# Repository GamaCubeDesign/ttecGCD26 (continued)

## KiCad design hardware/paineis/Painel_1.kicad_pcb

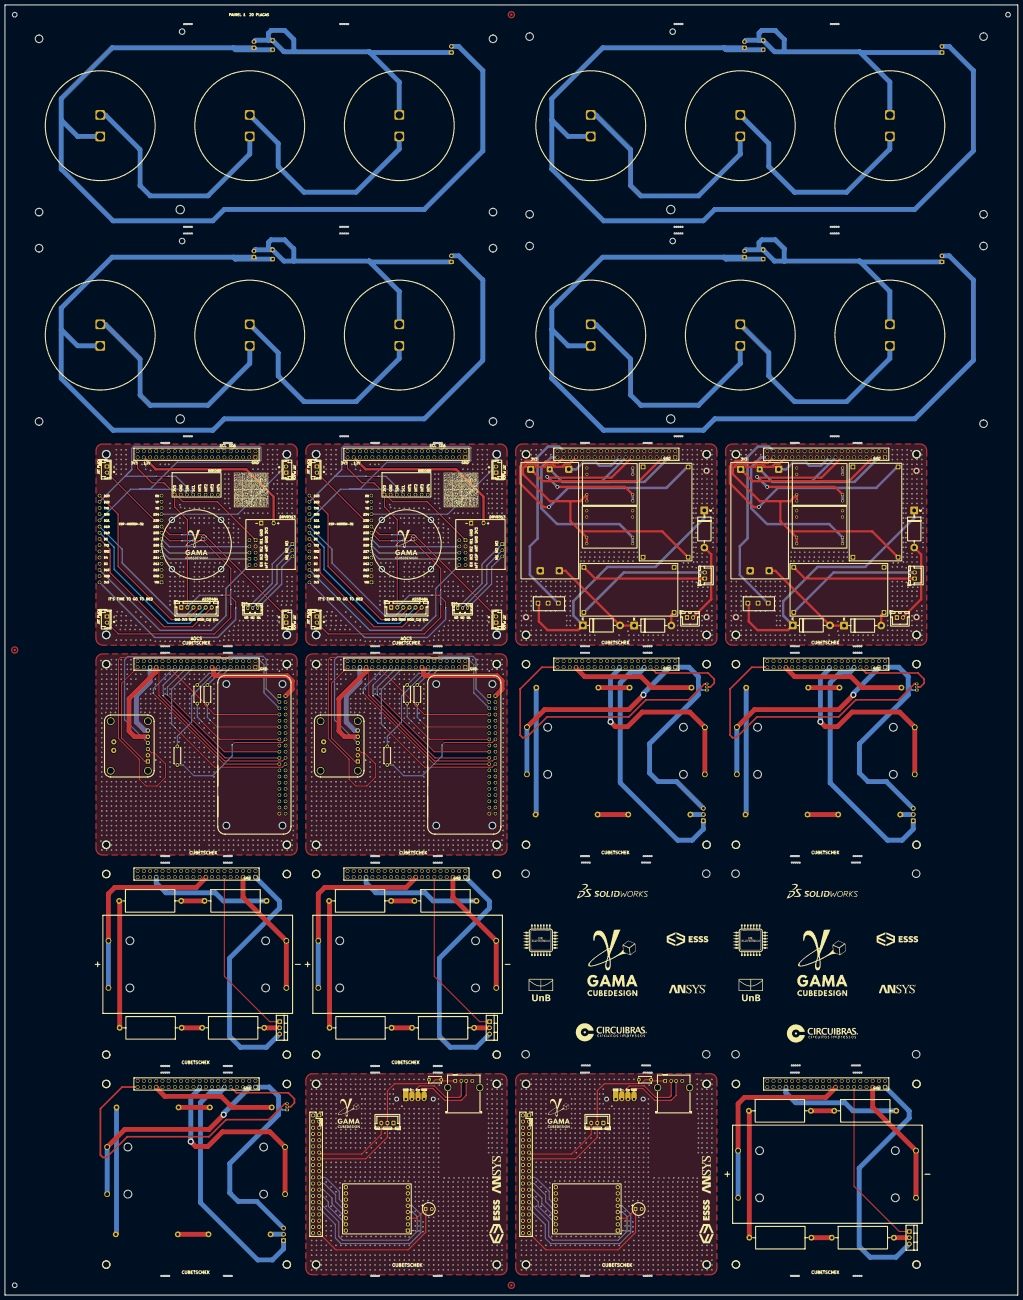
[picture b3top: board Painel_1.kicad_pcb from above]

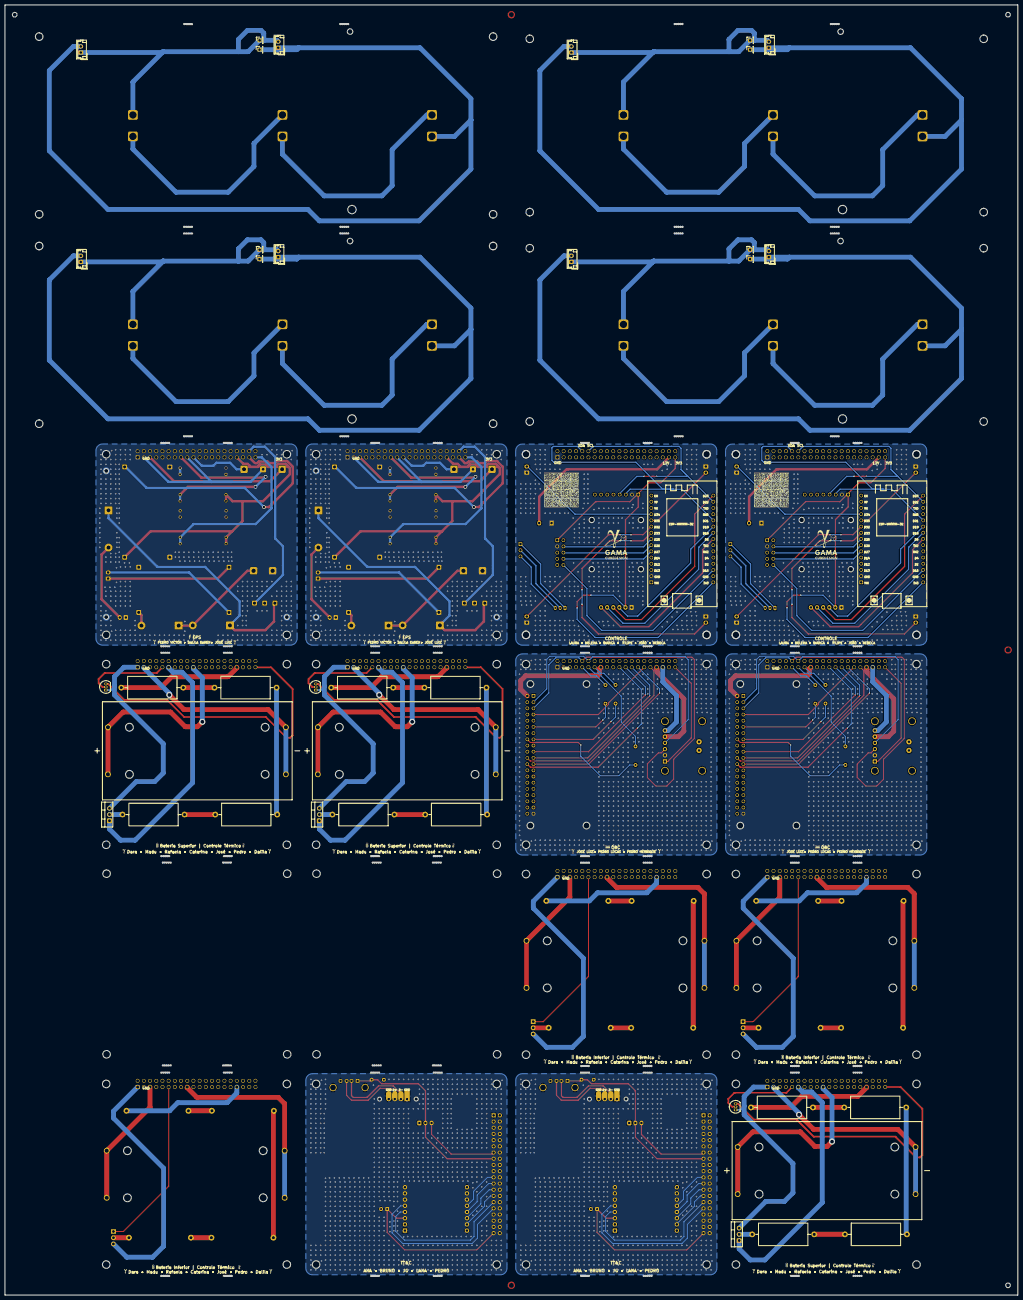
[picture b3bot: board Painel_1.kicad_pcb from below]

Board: 2 copper layers, 415.0 x 528.6 mm, 669 parts (79 on the bottom side), 208 nets.

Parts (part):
AOCS_1_1_AS5048A2, AOCS_2_1_AS5048A2: AS5048A
AOCS_1_2_REF**, AOCS_1_4_REF**, AOCS_1_7_REF**, AOCS_1_9_REF**, AOCS_2_2_REF**, AOCS_2_4_REF**, AOCS_2_7_REF**, AOCS_2_9_REF**: furo
AOCS_1_3_DRV8313, AOCS_2_3_DRV8313: DRV8313; DRV3813
AOCS_1_5_X+1, AOCS_1_12_Y-1, AOCS_1_13_X-1, AOCS_1_14_Y+1, AOCS_2_5_X+1, AOCS_2_12_Y-1, AOCS_2_13_X-1, AOCS_2_14_Y+1: JST; JST_PLACA
AOCS_1_6_Barramento1, AOCS_2_6_Barramento1: Barramento
AOCS_1_8_logo, AOCS_1_18_logo, AOCS_2_8_logo, AOCS_2_18_logo: LOGO; logo
AOCS_1_10_G***, AOCS_1_17_G***, AOCS_2_10_G***, AOCS_2_17_G***: LOGO; data
AOCS_1_11_GM2804, AOCS_2_11_GM2804: GM2804; GM2804_Molex_KK-3p-254
AOCS_1_15_BMI008, AOCS_2_15_BMI008: BMI088
AOCS_1_16_ESP32, AOCS_2_16_ESP32: ESP32; ESP32-30p
EPS_1_1_D3, EPS_1_12_D2, EPS_1_16_D1, EPS_2_1_D3, EPS_2_12_D2, EPS_2_16_D1: 1N5822; D_DO-201AD_P15.24mm_Horizontal
EPS_1_2_MP1584_Module2, EPS_1_4_MP1584_Module1, EPS_2_2_MP1584_Module2, EPS_2_4_MP1584_Module1: MP1584_MODULE
EPS_1_3_J3, EPS_1_17_J2, EPS_2_3_J3, EPS_2_17_J2: Conn_01x02_Pin; JST_XH_B2B-XH-A_1x02_P2.50mm_Vertical
EPS_1_5_G***, EPS_1_18_G***, EPS_1_19_G***, EPS_1_20_G***, EPS_1_CIMA_1_7_G***, EPS_1_CIMA_1_9_G***, EPS_1_CIMA_1_10_G***, EPS_1_CIMA_1_16_G***, EPS_1_CIMA_2_7_G***, EPS_1_CIMA_2_9_G***, EPS_1_CIMA_2_10_G***, EPS_1_CIMA_2_16_G***, EPS_1_CIMA_3_7_G***, EPS_1_CIMA_3_9_G***, EPS_1_CIMA_3_10_G***, EPS_1_CIMA_3_16_G***, EPS_2_5_G***, EPS_2_18_G***, EPS_2_19_G***, EPS_2_20_G***, EPS_2_BAIXO_1_12_G***, EPS_2_BAIXO_1_13_G***, EPS_2_BAIXO_1_14_G***, EPS_2_BAIXO_1_15_G***, EPS_2_BAIXO_2_12_G***, EPS_2_BAIXO_2_13_G***, EPS_2_BAIXO_2_14_G***, EPS_2_BAIXO_2_15_G***, EPS_2_BAIXO_3_12_G***, EPS_2_BAIXO_3_13_G***, EPS_2_BAIXO_3_14_G***, EPS_2_BAIXO_3_15_G***: LOGO
EPS_1_6_, EPS_1_9_, EPS_1_11_, EPS_1_13_, EPS_1_CIMA_1_1_, EPS_1_CIMA_1_3_, EPS_1_CIMA_1_4_, EPS_1_CIMA_1_5_, EPS_1_CIMA_2_1_, EPS_1_CIMA_2_3_, EPS_1_CIMA_2_4_, EPS_1_CIMA_2_5_, EPS_1_CIMA_3_1_, EPS_1_CIMA_3_3_, EPS_1_CIMA_3_4_, EPS_1_CIMA_3_5_, EPS_2_6_, EPS_2_9_, EPS_2_11_, EPS_2_13_, EPS_2_BAIXO_1_3_, EPS_2_BAIXO_1_6_, EPS_2_BAIXO_1_8_, EPS_2_BAIXO_1_11_, EPS_2_BAIXO_2_3_, EPS_2_BAIXO_2_6_, EPS_2_BAIXO_2_8_, EPS_2_BAIXO_2_11_, EPS_2_BAIXO_3_3_, EPS_2_BAIXO_3_6_, EPS_2_BAIXO_3_8_, EPS_2_BAIXO_3_11_: MountingHole_3.20mm
EPS_1_7_J1, EPS_1_CIMA_1_2_J1, EPS_1_CIMA_2_2_J1, EPS_1_CIMA_3_2_J1, EPS_2_7_J1, EPS_2_BAIXO_1_4_J1, EPS_2_BAIXO_2_4_J1, EPS_2_BAIXO_3_4_J1: Conn_02x20_Odd_Even; PC104_PSTD-2.54-2X20P
EPS_1_8_BMS-HX-2S-JH20, EPS_2_8_BMS-HX-2S-JH20: HX-2S-JH20
EPS_1_10_U1, EPS_1_15_U2, EPS_2_10_U1, EPS_2_15_U2: TPS61088
EPS_1_14_SW1, EPS_2_14_SW1: SW_SPDT; KW10
EPS_1_CIMA_1_6_Q1, EPS_1_CIMA_2_6_Q1, EPS_1_CIMA_3_6_Q1, EPS_2_BAIXO_1_5_Q1, EPS_2_BAIXO_2_5_Q1, EPS_2_BAIXO_3_5_Q1: TIP120; TO-220-3_Vertical
EPS_1_CIMA_1_8_R1, EPS_1_CIMA_1_11_R3, EPS_1_CIMA_1_12_R2, EPS_1_CIMA_1_15_R4, EPS_1_CIMA_2_8_R1, EPS_1_CIMA_2_11_R3, EPS_1_CIMA_2_12_R2, EPS_1_CIMA_2_15_R4, EPS_1_CIMA_3_8_R1, EPS_1_CIMA_3_11_R3, EPS_1_CIMA_3_12_R2, EPS_1_CIMA_3_15_R4, EPS_2_BAIXO_1_1_R2, EPS_2_BAIXO_1_2_R1, EPS_2_BAIXO_1_9_R3, EPS_2_BAIXO_1_10_R4, EPS_2_BAIXO_2_1_R2, EPS_2_BAIXO_2_2_R1, EPS_2_BAIXO_2_9_R3, EPS_2_BAIXO_2_10_R4, EPS_2_BAIXO_3_1_R2, EPS_2_BAIXO_3_2_R1, EPS_2_BAIXO_3_9_R3, EPS_2_BAIXO_3_10_R4: Heater; R_Axial_DIN0922_L20.0mm_D9.0mm_P25.40mm_Horizontal
EPS_1_CIMA_1_13_BT1, EPS_1_CIMA_2_13_BT1, EPS_1_CIMA_3_13_BT1, EPS_2_BAIXO_1_7_BT1, EPS_2_BAIXO_2_7_BT1, EPS_2_BAIXO_3_7_BT1: BK-18650-PC4; BAT_BK-18650-PC4
EPS_1_CIMA_1_14_U1, EPS_1_CIMA_2_14_U1, EPS_1_CIMA_3_14_U1: DS18B20; TO-92_Inline
FID_1_1, FID_1_2, FID_1_3: Fiducial_Donut_1_2_3
MB_AOCS_1_bottom_1_1, MB_AOCS_1_bottom_1_2, MB_AOCS_1_bottom_1_3, MB_AOCS_1_bottom_1_4, MB_AOCS_1_bottom_1_5, MB_AOCS_1_bottom_2_1, MB_AOCS_1_bottom_2_2, MB_AOCS_1_bottom_2_3, MB_AOCS_1_bottom_2_4, MB_AOCS_1_bottom_2_5, MB_AOCS_1_top_1_1, MB_AOCS_1_top_1_2, MB_AOCS_1_top_1_3, MB_AOCS_1_top_1_4, MB_AOCS_1_top_1_5, MB_AOCS_1_top_2_1, MB_AOCS_1_top_2_2, MB_AOCS_1_top_2_3, MB_AOCS_1_top_2_4, MB_AOCS_1_top_2_5, MB_AOCS_2_bottom_1_1, MB_AOCS_2_bottom_1_2, MB_AOCS_2_bottom_1_3, MB_AOCS_2_bottom_1_4, MB_AOCS_2_bottom_1_5, MB_AOCS_2_bottom_2_1, MB_AOCS_2_bottom_2_2, MB_AOCS_2_bottom_2_3, MB_AOCS_2_bottom_2_4, MB_AOCS_2_bottom_2_5, MB_AOCS_2_top_1_1, MB_AOCS_2_top_1_2, MB_AOCS_2_top_1_3, MB_AOCS_2_top_1_4, MB_AOCS_2_top_1_5, MB_AOCS_2_top_2_1, MB_AOCS_2_top_2_2, MB_AOCS_2_top_2_3, MB_AOCS_2_top_2_4, MB_AOCS_2_top_2_5: NPTH
MB_EPS_1_CIMA_1_bottom_1_1, MB_EPS_1_CIMA_1_bottom_1_2, MB_EPS_1_CIMA_1_bottom_1_3, MB_EPS_1_CIMA_1_bottom_1_4, MB_EPS_1_CIMA_1_bottom_1_5, MB_EPS_1_CIMA_1_bottom_2_1, MB_EPS_1_CIMA_1_bottom_2_2, MB_EPS_1_CIMA_1_bottom_2_3, MB_EPS_1_CIMA_1_bottom_2_4, MB_EPS_1_CIMA_1_bottom_2_5, MB_EPS_1_CIMA_1_top_1_1, MB_EPS_1_CIMA_1_top_1_2, MB_EPS_1_CIMA_1_top_1_3, MB_EPS_1_CIMA_1_top_1_4, MB_EPS_1_CIMA_1_top_1_5, MB_EPS_1_CIMA_1_top_2_1, MB_EPS_1_CIMA_1_top_2_2, MB_EPS_1_CIMA_1_top_2_3, MB_EPS_1_CIMA_1_top_2_4, MB_EPS_1_CIMA_1_top_2_5, MB_EPS_1_CIMA_2_bottom_1_1, MB_EPS_1_CIMA_2_bottom_1_2, MB_EPS_1_CIMA_2_bottom_1_3, MB_EPS_1_CIMA_2_bottom_1_4, MB_EPS_1_CIMA_2_bottom_1_5, MB_EPS_1_CIMA_2_bottom_2_1, MB_EPS_1_CIMA_2_bottom_2_2, MB_EPS_1_CIMA_2_bottom_2_3, MB_EPS_1_CIMA_2_bottom_2_4, MB_EPS_1_CIMA_2_bottom_2_5, MB_EPS_1_CIMA_2_top_1_1, MB_EPS_1_CIMA_2_top_1_2, MB_EPS_1_CIMA_2_top_1_3, MB_EPS_1_CIMA_2_top_1_4, MB_EPS_1_CIMA_2_top_1_5, MB_EPS_1_CIMA_2_top_2_1, MB_EPS_1_CIMA_2_top_2_2, MB_EPS_1_CIMA_2_top_2_3, MB_EPS_1_CIMA_2_top_2_4, MB_EPS_1_CIMA_2_top_2_5, MB_EPS_1_CIMA_3_bottom_1_1, MB_EPS_1_CIMA_3_bottom_1_2, MB_EPS_1_CIMA_3_bottom_1_3, MB_EPS_1_CIMA_3_bottom_1_4, MB_EPS_1_CIMA_3_bottom_1_5, MB_EPS_1_CIMA_3_bottom_2_1, MB_EPS_1_CIMA_3_bottom_2_2, MB_EPS_1_CIMA_3_bottom_2_3, MB_EPS_1_CIMA_3_bottom_2_4, MB_EPS_1_CIMA_3_bottom_2_5, MB_EPS_1_CIMA_3_top_1_1, MB_EPS_1_CIMA_3_top_1_2, MB_EPS_1_CIMA_3_top_1_3, MB_EPS_1_CIMA_3_top_1_4, MB_EPS_1_CIMA_3_top_1_5, MB_EPS_1_CIMA_3_top_2_1, MB_EPS_1_CIMA_3_top_2_2, MB_EPS_1_CIMA_3_top_2_3, MB_EPS_1_CIMA_3_top_2_4, MB_EPS_1_CIMA_3_top_2_5, MB_EPS_1_bottom_1_1, MB_EPS_1_bottom_1_2, MB_EPS_1_bottom_1_3, MB_EPS_1_bottom_1_4, MB_EPS_1_bottom_1_5, MB_EPS_1_bottom_2_1, MB_EPS_1_bottom_2_2, MB_EPS_1_bottom_2_3, MB_EPS_1_bottom_2_4, MB_EPS_1_bottom_2_5, MB_EPS_1_top_1_1, MB_EPS_1_top_1_2, MB_EPS_1_top_1_3, MB_EPS_1_top_1_4, MB_EPS_1_top_1_5, MB_EPS_1_top_2_1, MB_EPS_1_top_2_2, MB_EPS_1_top_2_3, MB_EPS_1_top_2_4, MB_EPS_1_top_2_5, MB_EPS_2_BAIXO_1_bottom_1_1, MB_EPS_2_BAIXO_1_bottom_1_2, MB_EPS_2_BAIXO_1_bottom_1_3, MB_EPS_2_BAIXO_1_bottom_1_4, MB_EPS_2_BAIXO_1_bottom_1_5, MB_EPS_2_BAIXO_1_bottom_2_1, MB_EPS_2_BAIXO_1_bottom_2_2, MB_EPS_2_BAIXO_1_bottom_2_3, MB_EPS_2_BAIXO_1_bottom_2_4, MB_EPS_2_BAIXO_1_bottom_2_5, MB_EPS_2_BAIXO_1_top_1_1, MB_EPS_2_BAIXO_1_top_1_2, MB_EPS_2_BAIXO_1_top_1_3, MB_EPS_2_BAIXO_1_top_1_4, MB_EPS_2_BAIXO_1_top_1_5, MB_EPS_2_BAIXO_1_top_2_1, MB_EPS_2_BAIXO_1_top_2_2, MB_EPS_2_BAIXO_1_top_2_3, MB_EPS_2_BAIXO_1_top_2_4, MB_EPS_2_BAIXO_1_top_2_5, MB_EPS_2_BAIXO_2_bottom_1_1, MB_EPS_2_BAIXO_2_bottom_1_2, MB_EPS_2_BAIXO_2_bottom_1_3, MB_EPS_2_BAIXO_2_bottom_1_4, MB_EPS_2_BAIXO_2_bottom_1_5, MB_EPS_2_BAIXO_2_bottom_2_1, MB_EPS_2_BAIXO_2_bottom_2_2, MB_EPS_2_BAIXO_2_bottom_2_3, MB_EPS_2_BAIXO_2_bottom_2_4, MB_EPS_2_BAIXO_2_bottom_2_5, MB_EPS_2_BAIXO_2_top_1_1, MB_EPS_2_BAIXO_2_top_1_2, MB_EPS_2_BAIXO_2_top_1_3, MB_EPS_2_BAIXO_2_top_1_4, MB_EPS_2_BAIXO_2_top_1_5, MB_EPS_2_BAIXO_2_top_2_1, MB_EPS_2_BAIXO_2_top_2_2, MB_EPS_2_BAIXO_2_top_2_3, MB_EPS_2_BAIXO_2_top_2_4, MB_EPS_2_BAIXO_2_top_2_5, MB_EPS_2_BAIXO_3_bottom_1_1, MB_EPS_2_BAIXO_3_bottom_1_2, MB_EPS_2_BAIXO_3_bottom_1_3, MB_EPS_2_BAIXO_3_bottom_1_4, MB_EPS_2_BAIXO_3_bottom_1_5, MB_EPS_2_BAIXO_3_bottom_2_1, MB_EPS_2_BAIXO_3_bottom_2_2, MB_EPS_2_BAIXO_3_bottom_2_3, MB_EPS_2_BAIXO_3_bottom_2_4, MB_EPS_2_BAIXO_3_bottom_2_5, MB_EPS_2_BAIXO_3_top_1_1, MB_EPS_2_BAIXO_3_top_1_2, MB_EPS_2_BAIXO_3_top_1_3, MB_EPS_2_BAIXO_3_top_1_4, MB_EPS_2_BAIXO_3_top_1_5, MB_EPS_2_BAIXO_3_top_2_1, MB_EPS_2_BAIXO_3_top_2_2, MB_EPS_2_BAIXO_3_top_2_3, MB_EPS_2_BAIXO_3_top_2_4, MB_EPS_2_BAIXO_3_top_2_5, MB_EPS_2_bottom_1_1, MB_EPS_2_bottom_1_2, MB_EPS_2_bottom_1_3, MB_EPS_2_bottom_1_4, MB_EPS_2_bottom_1_5, MB_EPS_2_bottom_2_1, MB_EPS_2_bottom_2_2, MB_EPS_2_bottom_2_3, MB_EPS_2_bottom_2_4, MB_EPS_2_bottom_2_5, MB_EPS_2_top_1_1, MB_EPS_2_top_1_2, MB_EPS_2_top_1_3, MB_EPS_2_top_1_4, MB_EPS_2_top_1_5, MB_EPS_2_top_2_1, MB_EPS_2_top_2_2, MB_EPS_2_top_2_3, MB_EPS_2_top_2_4, MB_EPS_2_top_2_5: NPTH
MB_OBC_1_bottom_1_1, MB_OBC_1_bottom_1_2, MB_OBC_1_bottom_1_3, MB_OBC_1_bottom_1_4, MB_OBC_1_bottom_1_5, MB_OBC_1_bottom_2_1, MB_OBC_1_bottom_2_2, MB_OBC_1_bottom_2_3, MB_OBC_1_bottom_2_4, MB_OBC_1_bottom_2_5, MB_OBC_1_top_1_1, MB_OBC_1_top_1_2, MB_OBC_1_top_1_3, MB_OBC_1_top_1_4, MB_OBC_1_top_1_5, MB_OBC_1_top_2_1, MB_OBC_1_top_2_2, MB_OBC_1_top_2_3, MB_OBC_1_top_2_4, MB_OBC_1_top_2_5, MB_OBC_2_bottom_1_1, MB_OBC_2_bottom_1_2, MB_OBC_2_bottom_1_3, MB_OBC_2_bottom_1_4, MB_OBC_2_bottom_1_5, MB_OBC_2_bottom_2_1, MB_OBC_2_bottom_2_2, MB_OBC_2_bottom_2_3, MB_OBC_2_bottom_2_4, MB_OBC_2_bottom_2_5, MB_OBC_2_top_1_1, MB_OBC_2_top_1_2, MB_OBC_2_top_1_3, MB_OBC_2_top_1_4, MB_OBC_2_top_1_5, MB_OBC_2_top_2_1, MB_OBC_2_top_2_2, MB_OBC_2_top_2_3, MB_OBC_2_top_2_4, MB_OBC_2_top_2_5: NPTH
MB_SOLAR_1_1_bottom_1_1, MB_SOLAR_1_1_bottom_1_2, MB_SOLAR_1_1_bottom_1_3, MB_SOLAR_1_1_bottom_1_4, MB_SOLAR_1_1_bottom_1_5, MB_SOLAR_1_1_bottom_2_1, MB_SOLAR_1_1_bottom_2_2, MB_SOLAR_1_1_bottom_2_3, MB_SOLAR_1_1_bottom_2_4, MB_SOLAR_1_1_bottom_2_5, MB_SOLAR_1_1_top_1_1, MB_SOLAR_1_1_top_1_2, MB_SOLAR_1_1_top_1_3, MB_SOLAR_1_1_top_1_4, MB_SOLAR_1_1_top_1_5, MB_SOLAR_1_1_top_2_1, MB_SOLAR_1_1_top_2_2, MB_SOLAR_1_1_top_2_3, MB_SOLAR_1_1_top_2_4, MB_SOLAR_1_1_top_2_5, MB_SOLAR_1_2_bottom_1_1, MB_SOLAR_1_2_bottom_1_2, MB_SOLAR_1_2_bottom_1_3, MB_SOLAR_1_2_bottom_1_4, MB_SOLAR_1_2_bottom_1_5, MB_SOLAR_1_2_bottom_2_1, MB_SOLAR_1_2_bottom_2_2, MB_SOLAR_1_2_bottom_2_3, MB_SOLAR_1_2_bottom_2_4, MB_SOLAR_1_2_bottom_2_5, MB_SOLAR_1_2_top_1_1, MB_SOLAR_1_2_top_1_2, MB_SOLAR_1_2_top_1_3, MB_SOLAR_1_2_top_1_4, MB_SOLAR_1_2_top_1_5, MB_SOLAR_1_2_top_2_1, MB_SOLAR_1_2_top_2_2, MB_SOLAR_1_2_top_2_3, MB_SOLAR_1_2_top_2_4, MB_SOLAR_1_2_top_2_5, MB_SOLAR_2_1_bottom_1_1, MB_SOLAR_2_1_bottom_1_2, MB_SOLAR_2_1_bottom_1_3, MB_SOLAR_2_1_bottom_1_4, MB_SOLAR_2_1_bottom_1_5, MB_SOLAR_2_1_bottom_2_1, MB_SOLAR_2_1_bottom_2_2, MB_SOLAR_2_1_bottom_2_3, MB_SOLAR_2_1_bottom_2_4, MB_SOLAR_2_1_bottom_2_5, MB_SOLAR_2_1_top_1_1, MB_SOLAR_2_1_top_1_2, MB_SOLAR_2_1_top_1_3, MB_SOLAR_2_1_top_1_4, MB_SOLAR_2_1_top_1_5, MB_SOLAR_2_1_top_2_1, MB_SOLAR_2_1_top_2_2, MB_SOLAR_2_1_top_2_3, MB_SOLAR_2_1_top_2_4, MB_SOLAR_2_1_top_2_5, MB_SOLAR_2_2_bottom_1_1, MB_SOLAR_2_2_bottom_1_2, MB_SOLAR_2_2_bottom_1_3, MB_SOLAR_2_2_bottom_1_4, MB_SOLAR_2_2_bottom_1_5, MB_SOLAR_2_2_bottom_2_1, MB_SOLAR_2_2_bottom_2_2, MB_SOLAR_2_2_bottom_2_3, MB_SOLAR_2_2_bottom_2_4, MB_SOLAR_2_2_bottom_2_5, MB_SOLAR_2_2_top_1_1, MB_SOLAR_2_2_top_1_2, MB_SOLAR_2_2_top_1_3, MB_SOLAR_2_2_top_1_4, MB_SOLAR_2_2_top_1_5, MB_SOLAR_2_2_top_2_1, MB_SOLAR_2_2_top_2_2, MB_SOLAR_2_2_top_2_3, MB_SOLAR_2_2_top_2_4, MB_SOLAR_2_2_top_2_5: NPTH
MB_TTEC_1_bottom_1_1, MB_TTEC_1_bottom_1_2, MB_TTEC_1_bottom_1_3, MB_TTEC_1_bottom_1_4, MB_TTEC_1_bottom_1_5, MB_TTEC_1_bottom_2_1, MB_TTEC_1_bottom_2_2, MB_TTEC_1_bottom_2_3, MB_TTEC_1_bottom_2_4, MB_TTEC_1_bottom_2_5, MB_TTEC_1_top_1_1, MB_TTEC_1_top_1_2, MB_TTEC_1_top_1_3, MB_TTEC_1_top_1_4, MB_TTEC_1_top_1_5, MB_TTEC_1_top_2_1, MB_TTEC_1_top_2_2, MB_TTEC_1_top_2_3, MB_TTEC_1_top_2_4, MB_TTEC_1_top_2_5, MB_TTEC_2_bottom_1_1, MB_TTEC_2_bottom_1_2, MB_TTEC_2_bottom_1_3, MB_TTEC_2_bottom_1_4, MB_TTEC_2_bottom_1_5, MB_TTEC_2_bottom_2_1, MB_TTEC_2_bottom_2_2, MB_TTEC_2_bottom_2_3, MB_TTEC_2_bottom_2_4, MB_TTEC_2_bottom_2_5, MB_TTEC_2_top_1_1, MB_TTEC_2_top_1_2, MB_TTEC_2_top_1_3, MB_TTEC_2_top_1_4, MB_TTEC_2_top_1_5, MB_TTEC_2_top_2_1, MB_TTEC_2_top_2_2, MB_TTEC_2_top_2_3, MB_TTEC_2_top_2_4, MB_TTEC_2_top_2_5: NPTH
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
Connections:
AOCS_1/GND: AOCS_1_1_AS5048A2.1 (GND), AOCS_1_3_DRV8313.1 (GND), AOCS_1_3_DRV8313.14 (GND), AOCS_1_5_X+1.1, AOCS_1_6_Barramento1.1, AOCS_1_12_Y-1.1, AOCS_1_13_X-1.1, AOCS_1_14_Y+1.1, AOCS_1_15_BMI008.2 (GND), AOCS_1_16_ESP32.2 (GND)
AOCS_1/Net-(AS5048A2-3V3): AOCS_1_1_AS5048A2.2 (3V3), AOCS_1_3_DRV8313.15 (3V3), AOCS_1_6_Barramento1.39, AOCS_1_15_BMI008.1 (3.3V), AOCS_1_16_ESP32.16 (3V3)
AOCS_1/Net-(AS5048A2-CLK): AOCS_1_1_AS5048A2.5 (CLK), AOCS_1_16_ESP32.24 (D18)
AOCS_1/Net-(AS5048A2-MISO): AOCS_1_1_AS5048A2.3 (MISO), AOCS_1_16_ESP32.25 (D19)
AOCS_1/Net-(AS5048A2-MOSI): AOCS_1_1_AS5048A2.4 (MOSI), AOCS_1_16_ESP32.30 (D23)
AOCS_1/Net-(AS5048A2-SCn): AOCS_1_1_AS5048A2.6 (SCn), AOCS_1_16_ESP32.23 (D5)
AOCS_1/Net-(BMI008-SCL): AOCS_1_6_Barramento1.12, AOCS_1_15_BMI008.4 (SCL), AOCS_1_16_ESP32.29 (D22)
AOCS_1/Net-(BMI008-SDA): AOCS_1_6_Barramento1.10, AOCS_1_15_BMI008.3 (SDA), AOCS_1_16_ESP32.26 (D21)
AOCS_1/Net-(Barramento1-Pin_37): AOCS_1_3_DRV8313.2 (VIN), AOCS_1_6_Barramento1.37
AOCS_1/Net-(DRV8313-EN): AOCS_1_3_DRV8313.6 (EN), AOCS_1_16_ESP32.18 (D15)
AOCS_1/Net-(DRV8313-IN1): AOCS_1_3_DRV8313.9 (IN1), AOCS_1_16_ESP32.8 (D25)
AOCS_1/Net-(DRV8313-IN2): AOCS_1_3_DRV8313.8 (IN2), AOCS_1_16_ESP32.7 (D26)
AOCS_1/Net-(DRV8313-IN3): AOCS_1_3_DRV8313.7 (IN3), AOCS_1_16_ESP32.6 (D27)
AOCS_1/Net-(DRV8313-M1): AOCS_1_3_DRV8313.3 (M1), AOCS_1_11_GM2804.1 (VIN)
AOCS_1/Net-(DRV8313-M2): AOCS_1_3_DRV8313.4 (M2), AOCS_1_11_GM2804.2 (GND)
AOCS_1/Net-(DRV8313-M3): AOCS_1_3_DRV8313.5 (M3), AOCS_1_11_GM2804.3 (PWM)
AOCS_1/Net-(ESP32-D32): AOCS_1_14_Y+1.2, AOCS_1_16_ESP32.10 (D32)
AOCS_1/Net-(ESP32-D33): AOCS_1_12_Y-1.2, AOCS_1_16_ESP32.9 (D33)
AOCS_1/Net-(ESP32-D34): AOCS_1_5_X+1.2, AOCS_1_16_ESP32.12 (D34)
AOCS_1/Net-(ESP32-D35): AOCS_1_13_X-1.2, AOCS_1_16_ESP32.11 (D35)
AOCS_2/GND: AOCS_2_1_AS5048A2.1 (GND), AOCS_2_3_DRV8313.1 (GND), AOCS_2_3_DRV8313.14 (GND), AOCS_2_5_X+1.1, AOCS_2_6_Barramento1.1, AOCS_2_12_Y-1.1, AOCS_2_13_X-1.1, AOCS_2_14_Y+1.1, AOCS_2_15_BMI008.2 (GND), AOCS_2_16_ESP32.2 (GND)
AOCS_2/Net-(AS5048A2-3V3): AOCS_2_1_AS5048A2.2 (3V3), AOCS_2_3_DRV8313.15 (3V3), AOCS_2_6_Barramento1.39, AOCS_2_15_BMI008.1 (3.3V), AOCS_2_16_ESP32.16 (3V3)
AOCS_2/Net-(AS5048A2-CLK): AOCS_2_1_AS5048A2.5 (CLK), AOCS_2_16_ESP32.24 (D18)
AOCS_2/Net-(AS5048A2-MISO): AOCS_2_1_AS5048A2.3 (MISO), AOCS_2_16_ESP32.25 (D19)
AOCS_2/Net-(AS5048A2-MOSI): AOCS_2_1_AS5048A2.4 (MOSI), AOCS_2_16_ESP32.30 (D23)
AOCS_2/Net-(AS5048A2-SCn): AOCS_2_1_AS5048A2.6 (SCn), AOCS_2_16_ESP32.23 (D5)
AOCS_2/Net-(BMI008-SCL): AOCS_2_6_Barramento1.12, AOCS_2_15_BMI008.4 (SCL), AOCS_2_16_ESP32.29 (D22)
AOCS_2/Net-(BMI008-SDA): AOCS_2_6_Barramento1.10, AOCS_2_15_BMI008.3 (SDA), AOCS_2_16_ESP32.26 (D21)
AOCS_2/Net-(Barramento1-Pin_37): AOCS_2_3_DRV8313.2 (VIN), AOCS_2_6_Barramento1.37
AOCS_2/Net-(DRV8313-EN): AOCS_2_3_DRV8313.6 (EN), AOCS_2_16_ESP32.18 (D15)
AOCS_2/Net-(DRV8313-IN1): AOCS_2_3_DRV8313.9 (IN1), AOCS_2_16_ESP32.8 (D25)
AOCS_2/Net-(DRV8313-IN2): AOCS_2_3_DRV8313.8 (IN2), AOCS_2_16_ESP32.7 (D26)
AOCS_2/Net-(DRV8313-IN3): AOCS_2_3_DRV8313.7 (IN3), AOCS_2_16_ESP32.6 (D27)
AOCS_2/Net-(DRV8313-M1): AOCS_2_3_DRV8313.3 (M1), AOCS_2_11_GM2804.1 (VIN)
AOCS_2/Net-(DRV8313-M2): AOCS_2_3_DRV8313.4 (M2), AOCS_2_11_GM2804.2 (GND)
AOCS_2/Net-(DRV8313-M3): AOCS_2_3_DRV8313.5 (M3), AOCS_2_11_GM2804.3 (PWM)
AOCS_2/Net-(ESP32-D32): AOCS_2_14_Y+1.2, AOCS_2_16_ESP32.10 (D32)
AOCS_2/Net-(ESP32-D33): AOCS_2_12_Y-1.2, AOCS_2_16_ESP32.9 (D33)
AOCS_2/Net-(ESP32-D34): AOCS_2_5_X+1.2, AOCS_2_16_ESP32.12 (D34)
AOCS_2/Net-(ESP32-D35): AOCS_2_13_X-1.2, AOCS_2_16_ESP32.11 (D35)
EPS_1//3V3: EPS_1_2_MP1584_Module2.4 (VOUT+), EPS_1_7_J1.39
EPS_1//5V: EPS_1_4_MP1584_Module1.4 (VOUT+), EPS_1_7_J1.15
EPS_1//8V(Bruto): EPS_1_7_J1.38, EPS_1_14_SW1.1 (A)
EPS_1//8V(Liq): EPS_1_2_MP1584_Module2.1 (VIN+), EPS_1_4_MP1584_Module1.1 (VIN+), EPS_1_7_J1.33, EPS_1_10_U1.1 (VIN+)
EPS_1//12V: EPS_1_7_J1.37, EPS_1_10_U1.4 (VOUT+)
EPS_1//GND: EPS_1_2_MP1584_Module2.2 (VIN-), EPS_1_2_MP1584_Module2.3 (VOUT-), EPS_1_4_MP1584_Module1.2 (VIN-), EPS_1_4_MP1584_Module1.3 (VOUT-), EPS_1_7_J1.1, EPS_1_7_J1.2, EPS_1_8_BMS-HX-2S-JH20.5 (P-), EPS_1_10_U1.2 (VIN-), EPS_1_10_U1.3 (VOUT-), EPS_1_15_U2.3 (VOUT-), EPS_1_17_J2.1
EPS_1//Negativo Bateria Inf: EPS_1_7_J1.5, EPS_1_8_BMS-HX-2S-JH20.3 (B-)
EPS_1//Negativo Bateria Sup: EPS_1_7_J1.3, EPS_1_7_J1.17, EPS_1_8_BMS-HX-2S-JH20.2 (BM)
EPS_1//Positivo Bateria Sup: EPS_1_7_J1.19, EPS_1_8_BMS-HX-2S-JH20.1 (B+)
EPS_1/Net-(BMS-HX-2S-JH20-P+): EPS_1_1_D3.1 (K), EPS_1_8_BMS-HX-2S-JH20.4 (P+), EPS_1_16_D1.2 (A)
EPS_1/Net-(D1-K): EPS_1_12_D2.1 (K), EPS_1_14_SW1.3 (C), EPS_1_16_D1.1 (K)
EPS_1/Net-(D2-A): EPS_1_12_D2.2 (A), EPS_1_17_J2.2
EPS_1/Net-(D3-A): EPS_1_1_D3.2 (A), EPS_1_15_U2.4 (VOUT+)
EPS_1/Net-(J3-Pin_1): EPS_1_3_J3.1, EPS_1_15_U2.2 (VIN-)
EPS_1/Net-(J3-Pin_2): EPS_1_3_J3.2, EPS_1_15_U2.1 (VIN+)
EPS_1_CIMA_1//3V3: EPS_1_CIMA_1_2_J1.39, EPS_1_CIMA_1_14_U1.3 (V_{DD})
EPS_1_CIMA_1//8VLiq: EPS_1_CIMA_1_2_J1.33, EPS_1_CIMA_1_8_R1.2
EPS_1_CIMA_1//DS18B20_Sup: EPS_1_CIMA_1_2_J1.9, EPS_1_CIMA_1_14_U1.2 (DQ)
EPS_1_CIMA_1//GND: EPS_1_CIMA_1_2_J1.1, EPS_1_CIMA_1_6_Q1.3 (E), EPS_1_CIMA_1_14_U1.1 (GND)
EPS_1_CIMA_1//GPIO_TIP120: EPS_1_CIMA_1_2_J1.11, EPS_1_CIMA_1_6_Q1.1 (B)
EPS_1_CIMA_1//Negativo Bateria Sup: EPS_1_CIMA_1_2_J1.3, EPS_1_CIMA_1_13_BT1.1-, EPS_1_CIMA_1_13_BT1.2-
EPS_1_CIMA_1//Positivo Bateria Sup: EPS_1_CIMA_1_2_J1.19, EPS_1_CIMA_1_13_BT1.1+, EPS_1_CIMA_1_13_BT1.2+
EPS_1_CIMA_1/Net-(Q1-C): EPS_1_CIMA_1_6_Q1.2 (C), EPS_1_CIMA_1_15_R4.2
EPS_1_CIMA_1/Net-(R1-Pad1): EPS_1_CIMA_1_8_R1.1, EPS_1_CIMA_1_12_R2.2
EPS_1_CIMA_1/Net-(R2-Pad1): EPS_1_CIMA_1_11_R3.2, EPS_1_CIMA_1_12_R2.1
EPS_1_CIMA_1/Net-(R3-Pad1): EPS_1_CIMA_1_11_R3.1, EPS_1_CIMA_1_15_R4.1
EPS_1_CIMA_2//3V3: EPS_1_CIMA_2_2_J1.39, EPS_1_CIMA_2_14_U1.3 (V_{DD})
EPS_1_CIMA_2//8VLiq: EPS_1_CIMA_2_2_J1.33, EPS_1_CIMA_2_8_R1.2
EPS_1_CIMA_2//DS18B20_Sup: EPS_1_CIMA_2_2_J1.9, EPS_1_CIMA_2_14_U1.2 (DQ)
EPS_1_CIMA_2//GND: EPS_1_CIMA_2_2_J1.1, EPS_1_CIMA_2_6_Q1.3 (E), EPS_1_CIMA_2_14_U1.1 (GND)
EPS_1_CIMA_2//GPIO_TIP120: EPS_1_CIMA_2_2_J1.11, EPS_1_CIMA_2_6_Q1.1 (B)
EPS_1_CIMA_2//Negativo Bateria Sup: EPS_1_CIMA_2_2_J1.3, EPS_1_CIMA_2_13_BT1.1-, EPS_1_CIMA_2_13_BT1.2-
EPS_1_CIMA_2//Positivo Bateria Sup: EPS_1_CIMA_2_2_J1.19, EPS_1_CIMA_2_13_BT1.1+, EPS_1_CIMA_2_13_BT1.2+
EPS_1_CIMA_2/Net-(Q1-C): EPS_1_CIMA_2_6_Q1.2 (C), EPS_1_CIMA_2_15_R4.2
EPS_1_CIMA_2/Net-(R1-Pad1): EPS_1_CIMA_2_8_R1.1, EPS_1_CIMA_2_12_R2.2
EPS_1_CIMA_2/Net-(R2-Pad1): EPS_1_CIMA_2_11_R3.2, EPS_1_CIMA_2_12_R2.1
EPS_1_CIMA_2/Net-(R3-Pad1): EPS_1_CIMA_2_11_R3.1, EPS_1_CIMA_2_15_R4.1
EPS_1_CIMA_3//3V3: EPS_1_CIMA_3_2_J1.39, EPS_1_CIMA_3_14_U1.3 (V_{DD})
EPS_1_CIMA_3//8VLiq: EPS_1_CIMA_3_2_J1.33, EPS_1_CIMA_3_8_R1.2
EPS_1_CIMA_3//DS18B20_Sup: EPS_1_CIMA_3_2_J1.9, EPS_1_CIMA_3_14_U1.2 (DQ)
EPS_1_CIMA_3//GND: EPS_1_CIMA_3_2_J1.1, EPS_1_CIMA_3_6_Q1.3 (E), EPS_1_CIMA_3_14_U1.1 (GND)
EPS_1_CIMA_3//GPIO_TIP120: EPS_1_CIMA_3_2_J1.11, EPS_1_CIMA_3_6_Q1.1 (B)
EPS_1_CIMA_3//Negativo Bateria Sup: EPS_1_CIMA_3_2_J1.3, EPS_1_CIMA_3_13_BT1.1-, EPS_1_CIMA_3_13_BT1.2-
EPS_1_CIMA_3//Positivo Bateria Sup: EPS_1_CIMA_3_2_J1.19, EPS_1_CIMA_3_13_BT1.1+, EPS_1_CIMA_3_13_BT1.2+
EPS_1_CIMA_3/Net-(Q1-C): EPS_1_CIMA_3_6_Q1.2 (C), EPS_1_CIMA_3_15_R4.2
EPS_1_CIMA_3/Net-(R1-Pad1): EPS_1_CIMA_3_8_R1.1, EPS_1_CIMA_3_12_R2.2
EPS_1_CIMA_3/Net-(R2-Pad1): EPS_1_CIMA_3_11_R3.2, EPS_1_CIMA_3_12_R2.1
EPS_1_CIMA_3/Net-(R3-Pad1): EPS_1_CIMA_3_11_R3.1, EPS_1_CIMA_3_15_R4.1
EPS_2//3V3: EPS_2_2_MP1584_Module2.4 (VOUT+), EPS_2_7_J1.39
EPS_2//5V: EPS_2_4_MP1584_Module1.4 (VOUT+), EPS_2_7_J1.15
EPS_2//8V(Bruto): EPS_2_7_J1.38, EPS_2_14_SW1.1 (A)
EPS_2//8V(Liq): EPS_2_2_MP1584_Module2.1 (VIN+), EPS_2_4_MP1584_Module1.1 (VIN+), EPS_2_7_J1.33, EPS_2_10_U1.1 (VIN+)
EPS_2//12V: EPS_2_7_J1.37, EPS_2_10_U1.4 (VOUT+)
EPS_2//GND: EPS_2_2_MP1584_Module2.2 (VIN-), EPS_2_2_MP1584_Module2.3 (VOUT-), EPS_2_4_MP1584_Module1.2 (VIN-), EPS_2_4_MP1584_Module1.3 (VOUT-), EPS_2_7_J1.1, EPS_2_7_J1.2, EPS_2_8_BMS-HX-2S-JH20.5 (P-), EPS_2_10_U1.2 (VIN-), EPS_2_10_U1.3 (VOUT-), EPS_2_15_U2.3 (VOUT-), EPS_2_17_J2.1
EPS_2//Negativo Bateria Inf: EPS_2_7_J1.5, EPS_2_8_BMS-HX-2S-JH20.3 (B-)
EPS_2//Negativo Bateria Sup: EPS_2_7_J1.3, EPS_2_7_J1.17, EPS_2_8_BMS-HX-2S-JH20.2 (BM)
EPS_2//Positivo Bateria Sup: EPS_2_7_J1.19, EPS_2_8_BMS-HX-2S-JH20.1 (B+)
EPS_2/Net-(BMS-HX-2S-JH20-P+): EPS_2_1_D3.1 (K), EPS_2_8_BMS-HX-2S-JH20.4 (P+), EPS_2_16_D1.2 (A)
EPS_2/Net-(D1-K): EPS_2_12_D2.1 (K), EPS_2_14_SW1.3 (C), EPS_2_16_D1.1 (K)
EPS_2/Net-(D2-A): EPS_2_12_D2.2 (A), EPS_2_17_J2.2
EPS_2/Net-(D3-A): EPS_2_1_D3.2 (A), EPS_2_15_U2.4 (VOUT+)
EPS_2/Net-(J3-Pin_1): EPS_2_3_J3.1, EPS_2_15_U2.2 (VIN-)
EPS_2/Net-(J3-Pin_2): EPS_2_3_J3.2, EPS_2_15_U2.1 (VIN+)
EPS_2_BAIXO_1//8VLiq: EPS_2_BAIXO_1_2_R1.2, EPS_2_BAIXO_1_4_J1.33
EPS_2_BAIXO_1//GND: EPS_2_BAIXO_1_4_J1.1, EPS_2_BAIXO_1_5_Q1.3 (E)
EPS_2_BAIXO_1//GPIO_TIP120: EPS_2_BAIXO_1_4_J1.11, EPS_2_BAIXO_1_5_Q1.1 (B)
EPS_2_BAIXO_1//Negativo Bateria Inf: EPS_2_BAIXO_1_4_J1.5, EPS_2_BAIXO_1_7_BT1.1-, EPS_2_BAIXO_1_7_BT1.2-
EPS_2_BAIXO_1//Positivo Bateria Inf: EPS_2_BAIXO_1_4_J1.17, EPS_2_BAIXO_1_7_BT1.1+, EPS_2_BAIXO_1_7_BT1.2+
EPS_2_BAIXO_1/Net-(Q1-C): EPS_2_BAIXO_1_5_Q1.2 (C), EPS_2_BAIXO_1_10_R4.2
EPS_2_BAIXO_1/Net-(R1-Pad1): EPS_2_BAIXO_1_1_R2.2, EPS_2_BAIXO_1_2_R1.1
EPS_2_BAIXO_1/Net-(R2-Pad1): EPS_2_BAIXO_1_1_R2.1, EPS_2_BAIXO_1_9_R3.2
EPS_2_BAIXO_1/Net-(R3-Pad1): EPS_2_BAIXO_1_9_R3.1, EPS_2_BAIXO_1_10_R4.1
EPS_2_BAIXO_2//8VLiq: EPS_2_BAIXO_2_2_R1.2, EPS_2_BAIXO_2_4_J1.33
EPS_2_BAIXO_2//GND: EPS_2_BAIXO_2_4_J1.1, EPS_2_BAIXO_2_5_Q1.3 (E)
EPS_2_BAIXO_2//GPIO_TIP120: EPS_2_BAIXO_2_4_J1.11, EPS_2_BAIXO_2_5_Q1.1 (B)
EPS_2_BAIXO_2//Negativo Bateria Inf: EPS_2_BAIXO_2_4_J1.5, EPS_2_BAIXO_2_7_BT1.1-, EPS_2_BAIXO_2_7_BT1.2-
EPS_2_BAIXO_2//Positivo Bateria Inf: EPS_2_BAIXO_2_4_J1.17, EPS_2_BAIXO_2_7_BT1.1+, EPS_2_BAIXO_2_7_BT1.2+
EPS_2_BAIXO_2/Net-(Q1-C): EPS_2_BAIXO_2_5_Q1.2 (C), EPS_2_BAIXO_2_10_R4.2
EPS_2_BAIXO_2/Net-(R1-Pad1): EPS_2_BAIXO_2_1_R2.2, EPS_2_BAIXO_2_2_R1.1
EPS_2_BAIXO_2/Net-(R2-Pad1): EPS_2_BAIXO_2_1_R2.1, EPS_2_BAIXO_2_9_R3.2
EPS_2_BAIXO_2/Net-(R3-Pad1): EPS_2_BAIXO_2_9_R3.1, EPS_2_BAIXO_2_10_R4.1
EPS_2_BAIXO_3//8VLiq: EPS_2_BAIXO_3_2_R1.2, EPS_2_BAIXO_3_4_J1.33
EPS_2_BAIXO_3//GND: EPS_2_BAIXO_3_4_J1.1, EPS_2_BAIXO_3_5_Q1.3 (E)
EPS_2_BAIXO_3//GPIO_TIP120: EPS_2_BAIXO_3_4_J1.11, EPS_2_BAIXO_3_5_Q1.1 (B)
EPS_2_BAIXO_3//Negativo Bateria Inf: EPS_2_BAIXO_3_4_J1.5, EPS_2_BAIXO_3_7_BT1.1-, EPS_2_BAIXO_3_7_BT1.2-
EPS_2_BAIXO_3//Positivo Bateria Inf: EPS_2_BAIXO_3_4_J1.17, EPS_2_BAIXO_3_7_BT1.1+, EPS_2_BAIXO_3_7_BT1.2+
EPS_2_BAIXO_3/Net-(Q1-C): EPS_2_BAIXO_3_5_Q1.2 (C), EPS_2_BAIXO_3_10_R4.2
EPS_2_BAIXO_3/Net-(R1-Pad1): EPS_2_BAIXO_3_1_R2.2, EPS_2_BAIXO_3_2_R1.1
EPS_2_BAIXO_3/Net-(R2-Pad1): EPS_2_BAIXO_3_1_R2.1, EPS_2_BAIXO_3_9_R3.2
EPS_2_BAIXO_3/Net-(R3-Pad1): EPS_2_BAIXO_3_9_R3.1, EPS_2_BAIXO_3_10_R4.1
OBC_1//3V3: OBC_1_5_J1.39, OBC_1_9_U2.1 (VCC)
OBC_1//5V: OBC_1_5_J1.15, OBC_1_10_U1.2 (5V_2)
OBC_1//8V Bruto: OBC_1_5_J1.35, OBC_1_9_U2.6 (VIN+)
OBC_1//8V(INA): OBC_1_5_J1.33, OBC_1_9_U2.5 (VIN-)
OBC_1//DIO0 LORA: OBC_1_5_J1.29, OBC_1_10_U1.7 (GPIO4/GPIO_GCLK)
OBC_1//DS18B20: OBC_1_5_J1.9, OBC_1_7_R1.1
OBC_1//GND: OBC_1_5_J1.1, OBC_1_9_U2.2 (GND), OBC_1_10_U1.39 (GND_39)
OBC_1//MISO LORA: OBC_1_5_J1.25, OBC_1_10_U1.21 (GPIO9/SPI_MISO)
OBC_1//MOSI LORA: OBC_1_5_J1.23, OBC_1_10_U1.19 (GPIO10/SPI_MOSI)
OBC_1//NSS LORA: OBC_1_5_J1.21, OBC_1_10_U1.24 (GPIO8/SPI_~CE0)
OBC_1//RESET LORA: OBC_1_5_J1.31, OBC_1_10_U1.22 (GPIO25/GPIO_GEN6)
OBC_1//SCK LORA: OBC_1_5_J1.27, OBC_1_10_U1.23 (GPIO11/SPI_SCLK)
OBC_1//SCL: OBC_1_5_J1.10, OBC_1_9_U2.3 (SCL), OBC_1_10_U1.5 (GPIO3/SCL)
OBC_1//SDA: OBC_1_5_J1.12, OBC_1_9_U2.4 (SDA), OBC_1_10_U1.3 (GPIO2/SDA1)
OBC_1//TIP120(CT): OBC_1_1_R3.2, OBC_1_5_J1.11
OBC_1//TIP120(Mec): OBC_1_5_J1.13, OBC_1_8_R2.1
OBC_1/Net-(U1-GPIO17/GPIO_GEN0): OBC_1_7_R1.2, OBC_1_10_U1.11 (GPIO17/GPIO_GEN0)
OBC_1/Net-(U1-GPIO22/GPIO_GEN3): OBC_1_8_R2.2, OBC_1_10_U1.15 (GPIO22/GPIO_GEN3)
OBC_1/Net-(U1-GPIO23/GPIO_GEN4): OBC_1_1_R3.1, OBC_1_10_U1.16 (GPIO23/GPIO_GEN4)
OBC_2//3V3: OBC_2_5_J1.39, OBC_2_9_U2.1 (VCC)
OBC_2//5V: OBC_2_5_J1.15, OBC_2_10_U1.2 (5V_2)
OBC_2//8V Bruto: OBC_2_5_J1.35, OBC_2_9_U2.6 (VIN+)
OBC_2//8V(INA): OBC_2_5_J1.33, OBC_2_9_U2.5 (VIN-)
OBC_2//DIO0 LORA: OBC_2_5_J1.29, OBC_2_10_U1.7 (GPIO4/GPIO_GCLK)
OBC_2//DS18B20: OBC_2_5_J1.9, OBC_2_7_R1.1
OBC_2//GND: OBC_2_5_J1.1, OBC_2_9_U2.2 (GND), OBC_2_10_U1.39 (GND_39)
OBC_2//MISO LORA: OBC_2_5_J1.25, OBC_2_10_U1.21 (GPIO9/SPI_MISO)
OBC_2//MOSI LORA: OBC_2_5_J1.23, OBC_2_10_U1.19 (GPIO10/SPI_MOSI)
OBC_2//NSS LORA: OBC_2_5_J1.21, OBC_2_10_U1.24 (GPIO8/SPI_~CE0)
OBC_2//RESET LORA: OBC_2_5_J1.31, OBC_2_10_U1.22 (GPIO25/GPIO_GEN6)
OBC_2//SCK LORA: OBC_2_5_J1.27, OBC_2_10_U1.23 (GPIO11/SPI_SCLK)
OBC_2//SCL: OBC_2_5_J1.10, OBC_2_9_U2.3 (SCL), OBC_2_10_U1.5 (GPIO3/SCL)
OBC_2//SDA: OBC_2_5_J1.12, OBC_2_9_U2.4 (SDA), OBC_2_10_U1.3 (GPIO2/SDA1)
OBC_2//TIP120(CT): OBC_2_1_R3.2, OBC_2_5_J1.11
OBC_2//TIP120(Mec): OBC_2_5_J1.13, OBC_2_8_R2.1
OBC_2/Net-(U1-GPIO17/GPIO_GEN0): OBC_2_7_R1.2, OBC_2_10_U1.11 (GPIO17/GPIO_GEN0)
OBC_2/Net-(U1-GPIO22/GPIO_GEN3): OBC_2_8_R2.2, OBC_2_10_U1.15 (GPIO22/GPIO_GEN3)
OBC_2/Net-(U1-GPIO23/GPIO_GEN4): OBC_2_1_R3.1, OBC_2_10_U1.16 (GPIO23/GPIO_GEN4)
SOLAR_1_1/Net-(SC40-+): SOLAR_1_1_1_SC40.1 (+), SOLAR_1_1_4_SaídaPainel1.1, SOLAR_1_1_5_SaidaSistema1.1 (Pin_1_1), SOLAR_1_1_7_SaídaAOCS1.2
SOLAR_1_1/Net-(SC40--): SOLAR_1_1_1_SC40.2 (-), SOLAR_1_1_2_SC41.1 (+)
SOLAR_1_1/Net-(SC41--): SOLAR_1_1_2_SC41.2 (-), SOLAR_1_1_3_SC42.1 (+)
SOLAR_1_1/Net-(SC42--): SOLAR_1_1_3_SC42.2 (-), SOLAR_1_1_4_SaídaPainel1.2, SOLAR_1_1_6_SaidaSistema2.1 (Pin_1_1), SOLAR_1_1_7_SaídaAOCS1.1
SOLAR_1_2/Net-(SC40-+): SOLAR_1_2_1_SC40.1 (+), SOLAR_1_2_4_SaídaPainel1.1, SOLAR_1_2_5_SaidaSistema1.1 (Pin_1_1), SOLAR_1_2_7_SaídaAOCS1.2
SOLAR_1_2/Net-(SC40--): SOLAR_1_2_1_SC40.2 (-), SOLAR_1_2_2_SC41.1 (+)
SOLAR_1_2/Net-(SC41--): SOLAR_1_2_2_SC41.2 (-), SOLAR_1_2_3_SC42.1 (+)
SOLAR_1_2/Net-(SC42--): SOLAR_1_2_3_SC42.2 (-), SOLAR_1_2_4_SaídaPainel1.2, SOLAR_1_2_6_SaidaSistema2.1 (Pin_1_1), SOLAR_1_2_7_SaídaAOCS1.1
SOLAR_2_1/Net-(SC40-+): SOLAR_2_1_1_SC40.1 (+), SOLAR_2_1_4_SaídaPainel1.1, SOLAR_2_1_5_SaidaSistema1.1 (Pin_1_1), SOLAR_2_1_7_SaídaAOCS1.2
SOLAR_2_1/Net-(SC40--): SOLAR_2_1_1_SC40.2 (-), SOLAR_2_1_2_SC41.1 (+)
SOLAR_2_1/Net-(SC41--): SOLAR_2_1_2_SC41.2 (-), SOLAR_2_1_3_SC42.1 (+)
SOLAR_2_1/Net-(SC42--): SOLAR_2_1_3_SC42.2 (-), SOLAR_2_1_4_SaídaPainel1.2, SOLAR_2_1_6_SaidaSistema2.1 (Pin_1_1), SOLAR_2_1_7_SaídaAOCS1.1
SOLAR_2_2/Net-(SC40-+): SOLAR_2_2_1_SC40.1 (+), SOLAR_2_2_4_SaídaPainel1.1, SOLAR_2_2_5_SaidaSistema1.1 (Pin_1_1), SOLAR_2_2_7_SaídaAOCS1.2
SOLAR_2_2/Net-(SC40--): SOLAR_2_2_1_SC40.2 (-), SOLAR_2_2_2_SC41.1 (+)
SOLAR_2_2/Net-(SC41--): SOLAR_2_2_2_SC41.2 (-), SOLAR_2_2_3_SC42.1 (+)
SOLAR_2_2/Net-(SC42--): SOLAR_2_2_3_SC42.2 (-), SOLAR_2_2_4_SaídaPainel1.2, SOLAR_2_2_6_SaidaSistema2.1 (Pin_1_1), SOLAR_2_2_7_SaídaAOCS1.1
TTEC_1/+3V3: TTEC_1_4_J3.39, TTEC_1_7_C3.1, TTEC_1_11_U1.3 (3V3)
TTEC_1/+5V: TTEC_1_1_J1.1 (VBUS), TTEC_1_3_J4.2, TTEC_1_4_J3.15, TTEC_1_8_C2.1
TTEC_1//LORA_DIO0: TTEC_1_4_J3.31, TTEC_1_11_U1.5 (DIO0)
TTEC_1//LORA_RST: TTEC_1_4_J3.29, TTEC_1_11_U1.4 (RST)
TTEC_1//SPI_MISO: TTEC_1_4_J3.23, TTEC_1_11_U1.13 (MISO)
TTEC_1//SPI_MOSI: TTEC_1_4_J3.25, TTEC_1_11_U1.14 (MOSI)
TTEC_1//SPI_NSS: TTEC_1_4_J3.27, TTEC_1_11_U1.15 (NSS)
TTEC_1//SPI_SCK: TTEC_1_4_J3.21, TTEC_1_11_U1.12 (SCK)
TTEC_1//USB_D+: TTEC_1_1_J1.3 (D+), TTEC_1_10_J2.3
TTEC_1//USB_D-: TTEC_1_1_J1.2 (D-), TTEC_1_10_J2.2
TTEC_1//sinal_mec: TTEC_1_3_J4.3, TTEC_1_4_J3.13
TTEC_1/GND: TTEC_1_1_J1.4 (GND), TTEC_1_1_J1.SH (Shield), TTEC_1_3_J4.1, TTEC_1_4_J3.1, TTEC_1_4_J3.2, TTEC_1_7_C3.2, TTEC_1_8_C2.2, TTEC_1_10_J2.1, TTEC_1_10_J2.4, TTEC_1_11_U1.1 (GND), TTEC_1_11_U1.2 (GND), TTEC_1_11_U1.9 (GND), TTEC_1_11_U1.16 (GND)
TTEC_2/+3V3: TTEC_2_4_J3.39, TTEC_2_7_C3.1, TTEC_2_11_U1.3 (3V3)
TTEC_2/+5V: TTEC_2_1_J1.1 (VBUS), TTEC_2_3_J4.2, TTEC_2_4_J3.15, TTEC_2_8_C2.1
TTEC_2//LORA_DIO0: TTEC_2_4_J3.31, TTEC_2_11_U1.5 (DIO0)
TTEC_2//LORA_RST: TTEC_2_4_J3.29, TTEC_2_11_U1.4 (RST)
TTEC_2//SPI_MISO: TTEC_2_4_J3.23, TTEC_2_11_U1.13 (MISO)
TTEC_2//SPI_MOSI: TTEC_2_4_J3.25, TTEC_2_11_U1.14 (MOSI)
TTEC_2//SPI_NSS: TTEC_2_4_J3.27, TTEC_2_11_U1.15 (NSS)
TTEC_2//SPI_SCK: TTEC_2_4_J3.21, TTEC_2_11_U1.12 (SCK)
TTEC_2//USB_D+: TTEC_2_1_J1.3 (D+), TTEC_2_10_J2.3
TTEC_2//USB_D-: TTEC_2_1_J1.2 (D-), TTEC_2_10_J2.2
TTEC_2//sinal_mec: TTEC_2_3_J4.3, TTEC_2_4_J3.13
TTEC_2/GND: TTEC_2_1_J1.4 (GND), TTEC_2_1_J1.SH (Shield), TTEC_2_3_J4.1, TTEC_2_4_J3.1, TTEC_2_4_J3.2, TTEC_2_7_C3.2, TTEC_2_8_C2.2, TTEC_2_10_J2.1, TTEC_2_10_J2.4, TTEC_2_11_U1.1 (GND), TTEC_2_11_U1.2 (GND), TTEC_2_11_U1.9 (GND), TTEC_2_11_U1.16 (GND)

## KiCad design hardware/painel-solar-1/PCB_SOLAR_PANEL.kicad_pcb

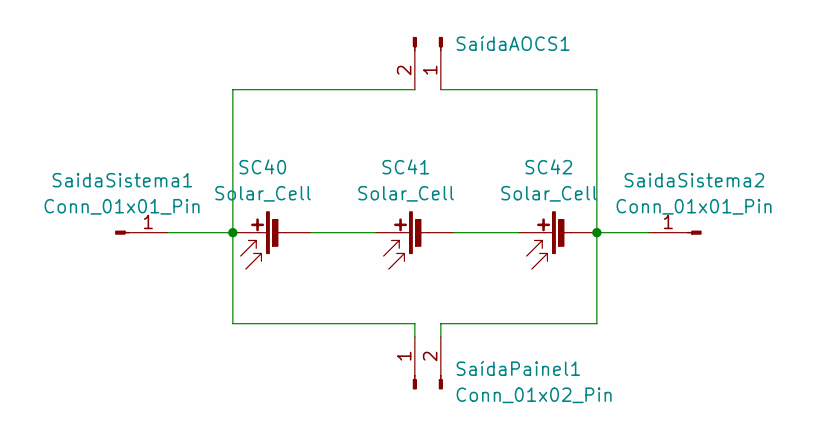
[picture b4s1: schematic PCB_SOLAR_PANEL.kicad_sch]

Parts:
SC40, SC41, SC42: Solar_Cell; Solar_Panel_45mm
SaidaSistema1, SaidaSistema2: Conn_01x01_Pin; PinSocket_1x01_P2.54mm_Vertical
SaídaAOCS1: Conn_01x02_Pin; JST_EH_B2B-EH-A_1x02_P2.50mm_Vertical
SaídaPainel1: Conn_01x02_Pin; JST_EH_B2B-EH-A_1x02_P2.50mm_Vertical

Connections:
unnamed: SC40.1 (+), SaidaSistema1.1 (Pin_1_1), SaídaAOCS1.2, SaídaPainel1.1
unnamed: SC40.2 (-), SC41.1 (+)
unnamed: SC41.2 (-), SC42.1 (+)
unnamed: SC42.2 (-), SaidaSistema2.1 (Pin_1_1), SaídaAOCS1.1, SaídaPainel1.2

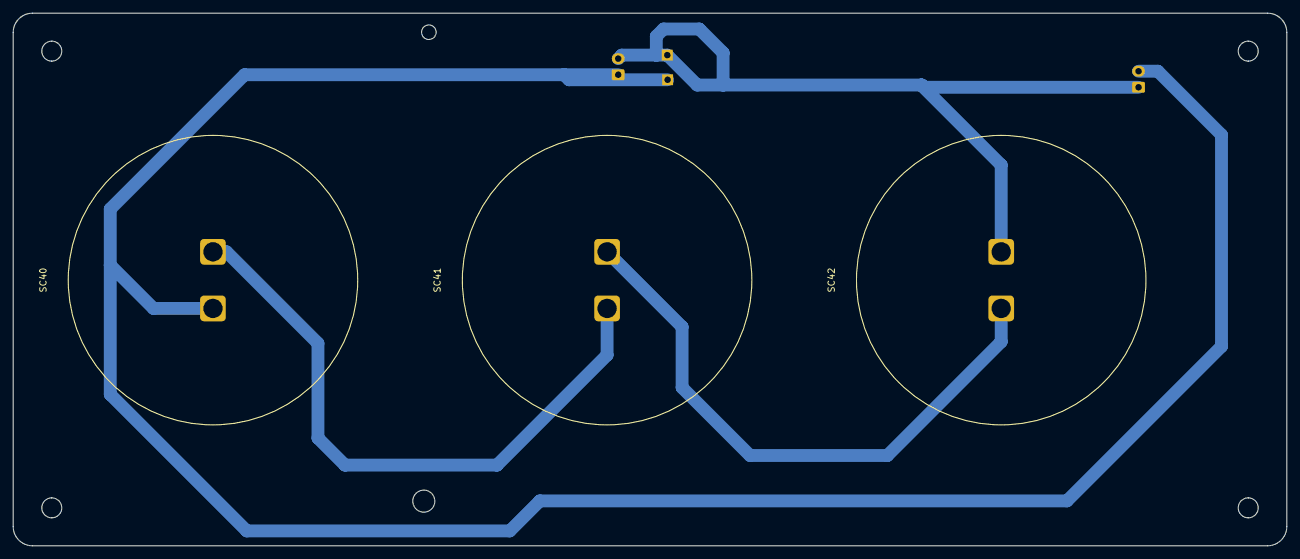
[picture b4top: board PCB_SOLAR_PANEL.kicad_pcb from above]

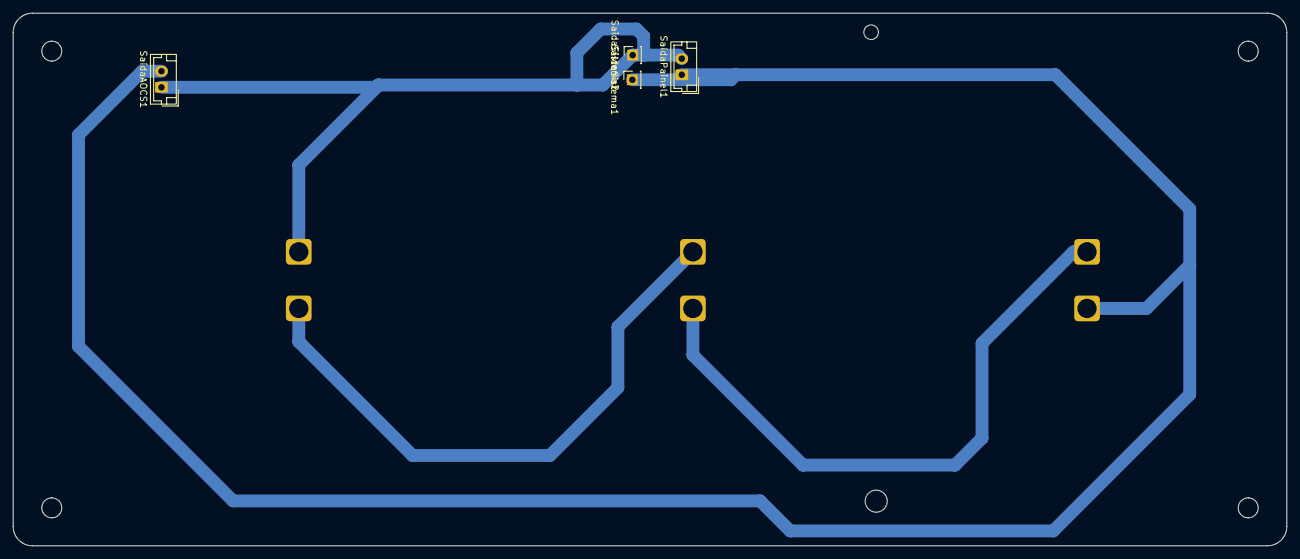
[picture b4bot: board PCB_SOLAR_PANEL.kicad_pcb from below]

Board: 2 copper layers, 198.0 x 82.8 mm, 7 parts (4 on the bottom side), 4 nets.
